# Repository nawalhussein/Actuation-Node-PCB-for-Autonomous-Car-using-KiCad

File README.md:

# STM32 Actuator Control Board PCB

This project contains the complete hardware design (schematics and PCB layout) and associated software for a custom-built STM32-based actuator control system to be put in the autonomous car.

### Brief Project Description

This PCB is designed as a centralized control hub for multiple DC motor actuators in an autonomous or complex electro-mechanical system (e.g., an agribot, mobile robot, or robotic manipulator).

At its core is an STM32 "BluePill" microcontroller. The board interfaces with various components to manage complex movement:

* **Microcontroller:** An STM32F103 (BluePill) provides the processing logic.
* **Actuator Drivers:** Integrated circuits (represented by connectors in the current schematic iteration) control multiple DC motors with direction (`DIR`) and pulse-width modulation (`PWM`) speed signals.
* **Control Input:** It receives motion and velocity commands via a high-level **CAN bus** or standard **UART** serial communication.
* **Feedback (ADC):** Analog inputs monitor potentiometer-based sensors (e.g., steering and brake feedback) for precise position sensing.
* **Interface (DAC):** A Digital-to-Analog converter provides fine-tuned analog voltage output.
* **Level Shifting:** Bidirectional level shifters ensure logic compatibility between 3.3V signals (like `STEP_EN`, `DIR_REAR_BRAKE`) and other standard 5V peripherals.
* **Safety:** A robust protection circuit with a reverse-voltage blocking diode and a fast-acting fuse ensures system reliability.
* **Expandability:** Multiple power sources and extra GPIO headers are included for external sensor integration and future features.

---

### Project Repository Contents

* `/hardware/`: Kicad design files (schematic and PCB)
* `/docs/`: PDF for the PCB and schematic

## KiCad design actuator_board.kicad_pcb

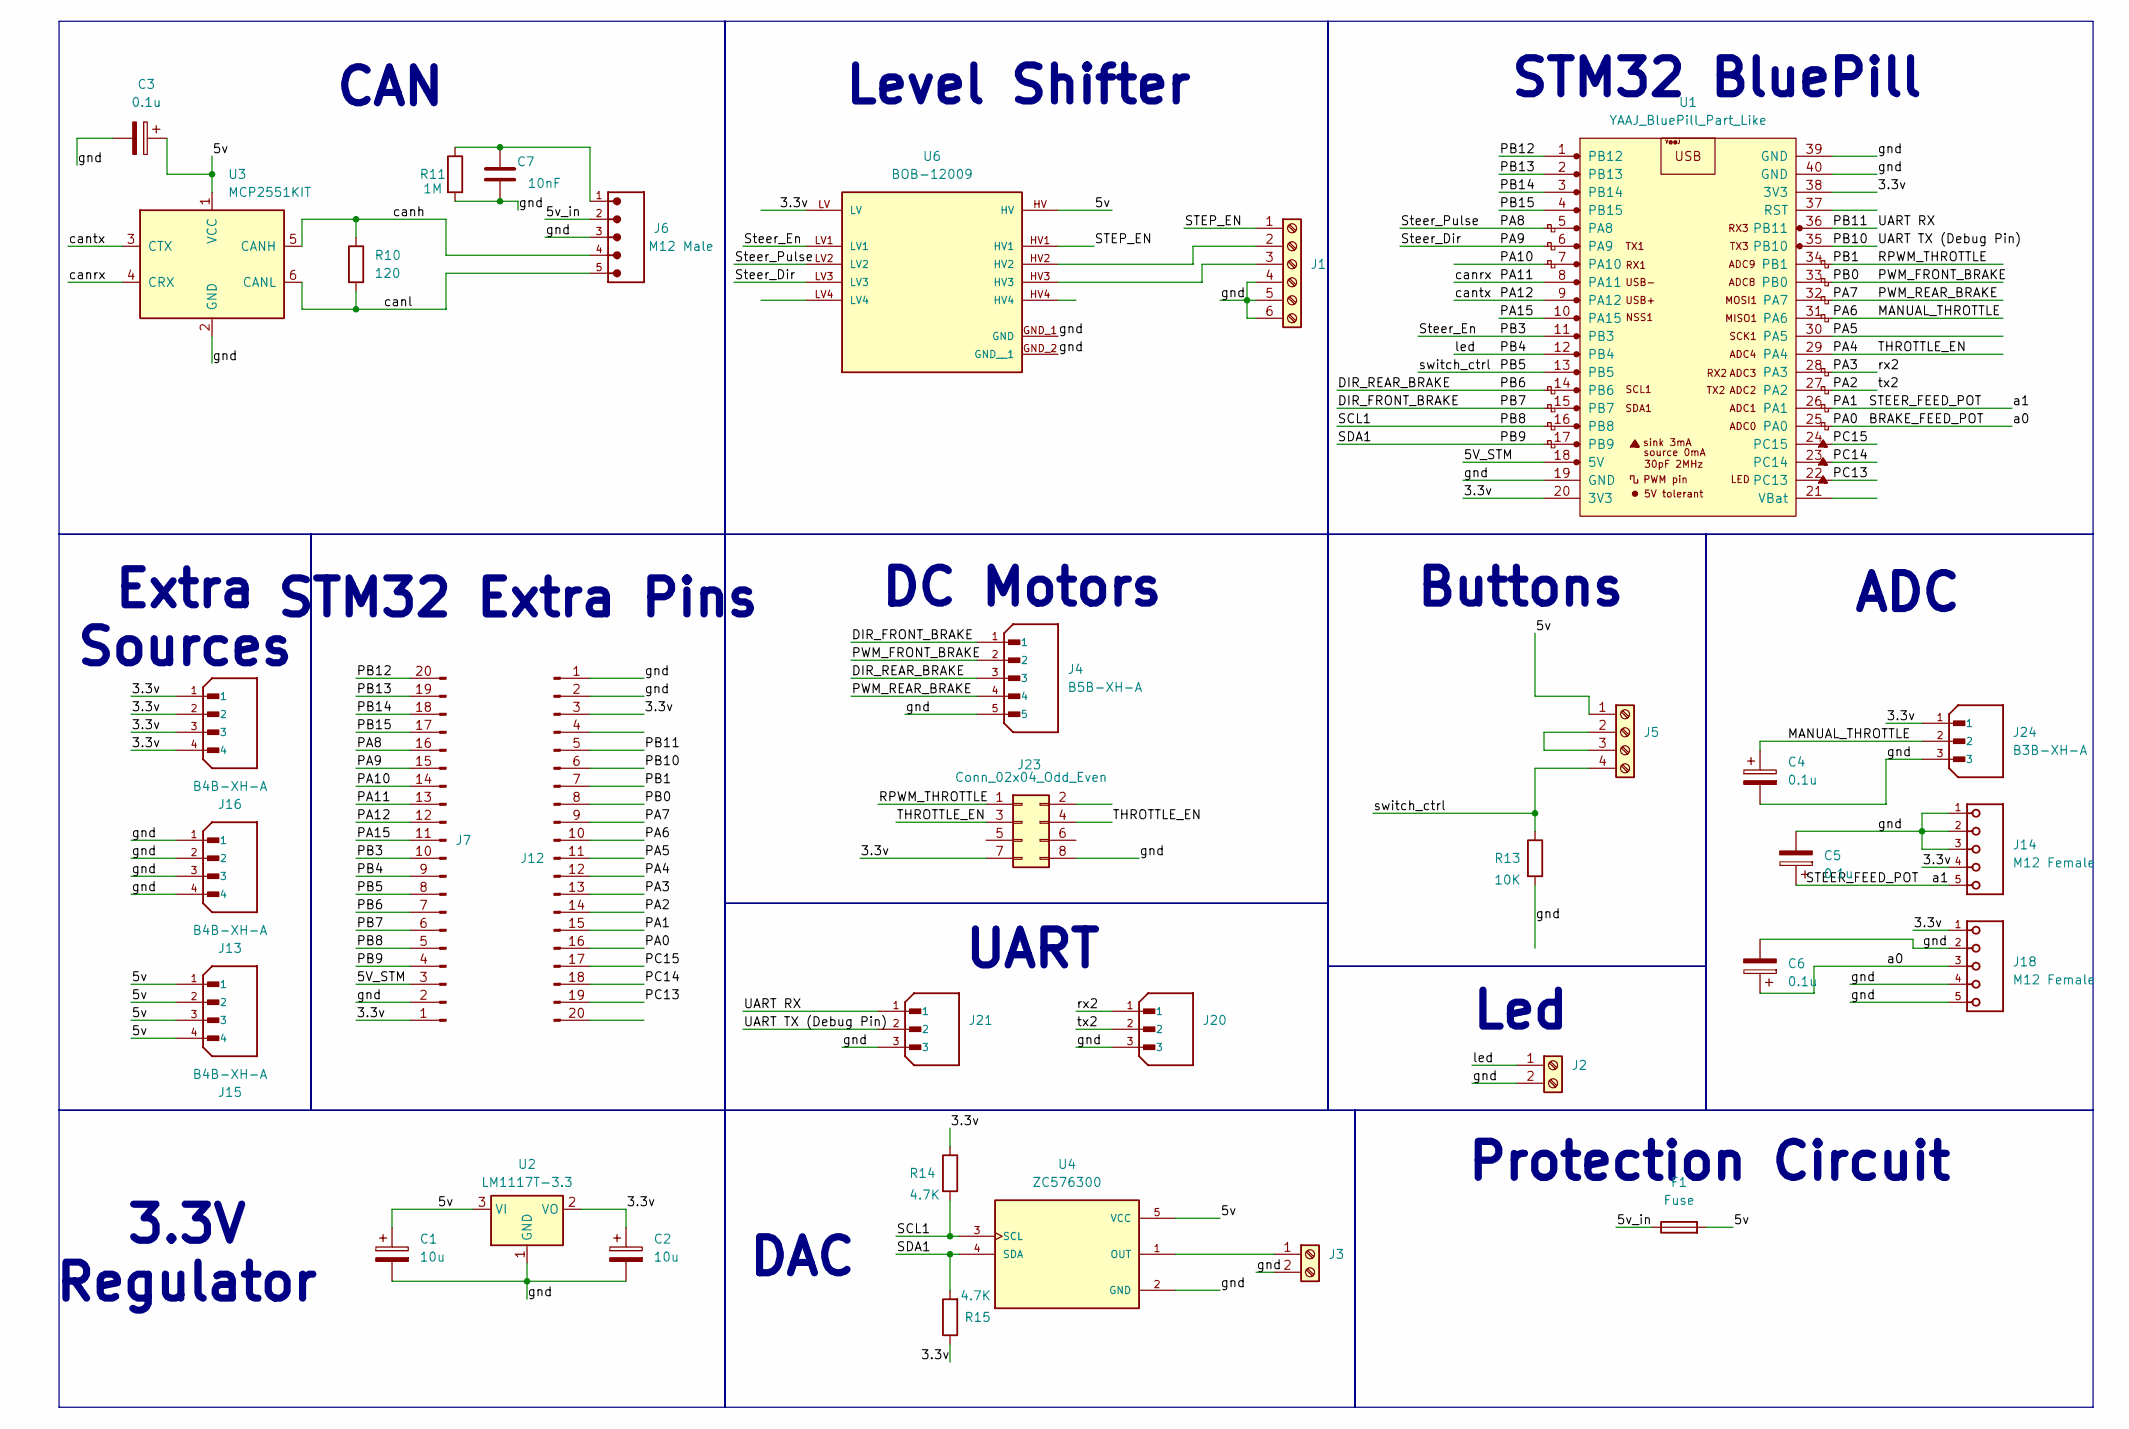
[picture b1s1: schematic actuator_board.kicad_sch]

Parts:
C1, C2: 10u; C_Disc_D6.0mm_W2.5mm_P5.00mm
C3, C4, C5, C6: 0.1u; C_Disc_D6.0mm_W2.5mm_P5.00mm
C7: 10nF; C_Disc_D6.0mm_W2.5mm_P5.00mm
F1: Fuse; Fuseholder_Cylinder-5x20mm_Schurter_0031_8201_Horizontal_Op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
J1: Screw_Terminal_01x06; TerminalBlock_Phoenix_MKDS-1,5-6-5.08_1x06_P5.08mm_Horizont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
J2, J3: Screw_Terminal_01x02; TE_282841-2
J4: B5B-XH-A; JST_B5B-XH-A; PARTREV 7/4/21
J5: Screw_Terminal_01x04; TE_282837-4
J6: M12 Male; 643270100305
J7, J12: Conn_01x20_Pin; PinSocket_1x20_P2.54mm_Vertical
J13, J15, J16: B4B-XH-A; JST_B4B-XH-A; PARTREV .
J14, J18: M12 Female; 643280100305
J20, J21, J24: B3B-XH-A; JST_B3B-XH-A; PARTREV .
J23: Conn_02x04_Odd_Even; IDC-Header_2x04_P2.54mm_Vertical
R10: 120; R_Axial_DIN0207_L6.3mm_D2.5mm_P10.16mm_Horizontal
R11: 1M; R_Axial_DIN0207_L6.3mm_D2.5mm_P10.16mm_Horizontal
R13: 10K; R_Axial_DIN0207_L6.3mm_D2.5mm_P10.16mm_Horizontal
R14, R15: 4.7K; R_Axial_DIN0207_L6.3mm_D2.5mm_P10.16mm_Horizontal
U1: YAAJ_BluePill_Part_Like; YAAJ_BluePill_1
U2: LM1117T-3.3; TO-220-3_Vertical
U3: MCP2551KIT; mcp2551kit
U4: ZC576300; MODULE_ZC576300; PARTREV v14
U6: BOB-12009; CONV_BOB-12009; PARTREV 01

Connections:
/3.3v: C2.1, J7.1, J12.3, J14.4, J16.1, J16.2, J16.3, J16.4, J18.1, J23.7, J24.1, R14.1, R15.1, U1.20 (3V3), U1.38 (3V3), U2.2 (VO), U6.LV
/5V_STM: J7.3, U1.18 (5V)
/5v: C1.1, C3.1, F1.2, J5.1, J15.1, J15.2, J15.3, J15.4, U2.3 (VI), U3.1 (VCC), U4.5 (VCC), U6.HV
/5v_in: F1.1, J6.2
/BRAKE_FEED_POT: C6.1, J12.16, J18.3, U1.25 (PA0)
/DIR_FRONT_BRAKE: J4.1, J7.6, U1.15 (PB7)
/DIR_REAR_BRAKE: J4.3, J7.7, U1.14 (PB6)
/MANUAL_THROTTLE: C4.1, J12.10, J24.2, U1.31 (PA6)
/PA1: C5.1, J12.15, J14.5, U1.26 (PA1)
/PA2: J12.14, J20.2, U1.27 (PA2)
/PA3: J12.13, J20.1, U1.28 (PA3)
/PA4: J12.12, J23.3, J23.4, U1.29 (PA4)
/PA5: J12.11, U1.30 (PA5)
/PA7: J4.4, J12.9, U1.32 (PA7)
/PA8: J7.16, U1.5 (PA8), U6.LV2
/PA9: J7.15, U1.6 (PA9), U6.LV3
/PA10: J7.14, U1.7 (PA10)
/PA11: J7.13, U1.8 (PA11), U3.4 (CRX)
/PA12: J7.12, U1.9 (PA12), U3.3 (CTX)
/PA15: J7.11, U1.10 (PA15)
/PB0: J4.2, J12.8, U1.33 (PB0)
/PB1: J12.7, J23.1, U1.34 (PB1)
/PB3: J7.10, U1.11 (PB3), U6.LV1
/PB4: J2.1, J7.9, U1.12 (PB4)
/PB5: J5.4, J7.8, R13.1, U1.13 (PB5)
/PB8: J7.5, R14.2, U1.16 (PB8), U4.3 (SCL)
/PB9: J7.4, R15.2, U1.17 (PB9), U4.4 (SDA)
/PB10: J12.6, J21.2, U1.35 (PB10)
/PB11: J12.5, J21.1, U1.36 (PB11)
/PB12: J7.20, U1.1 (PB12)
/PB13: J7.19, U1.2 (PB13)
/PB14: J7.18, U1.3 (PB14)
/PB15: J7.17, U1.4 (PB15)
/PC13: J12.19, U1.22 (PC13)
/PC14: J12.18, U1.23 (PC14)
/PC15: J12.17, U1.24 (PC15)
/STEP_EN: J1.1, U6.HV1
/canh: J6.4, R10.1, U3.5 (CANH)
/canl: J6.5, R10.2, U3.6 (CANL)
GND: C1.2, C2.2, C3.2, C4.2, C5.2, C6.2, C7.2, J1.4, J1.5, J1.6, J2.2, J3.2, J4.5, J6.3, J7.2, J12.1, J12.2, J13.1, J13.2, J13.3, J13.4, J14.1, J14.2, J14.3, J18.2, J18.4, J18.5, J20.3, J21.3, J23.8, J24.3, R11.2, R13.2, U1.19 (GND), U1.39 (GND), U1.40 (GND), U2.1 (GND), U3.2 (GND), U4.2 (GND), U4.6 (GND), U6.GND_1 (GND), U6.GND_2 (GND__1)
unnamed: C7.1, J6.1, R11.1
unnamed: J1.2, U6.HV2
unnamed: J1.3, U6.HV3
unnamed: J3.1, U4.1 (OUT)
unnamed: J5.2, J5.3

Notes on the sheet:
DC Motors
CAN
UART
STM32 Extra Pins
STM32 BluePill
ADC
Led
Level Shifter
Protection Circuit
DAC
Extra Sources
3.3V Regulator
Buttons

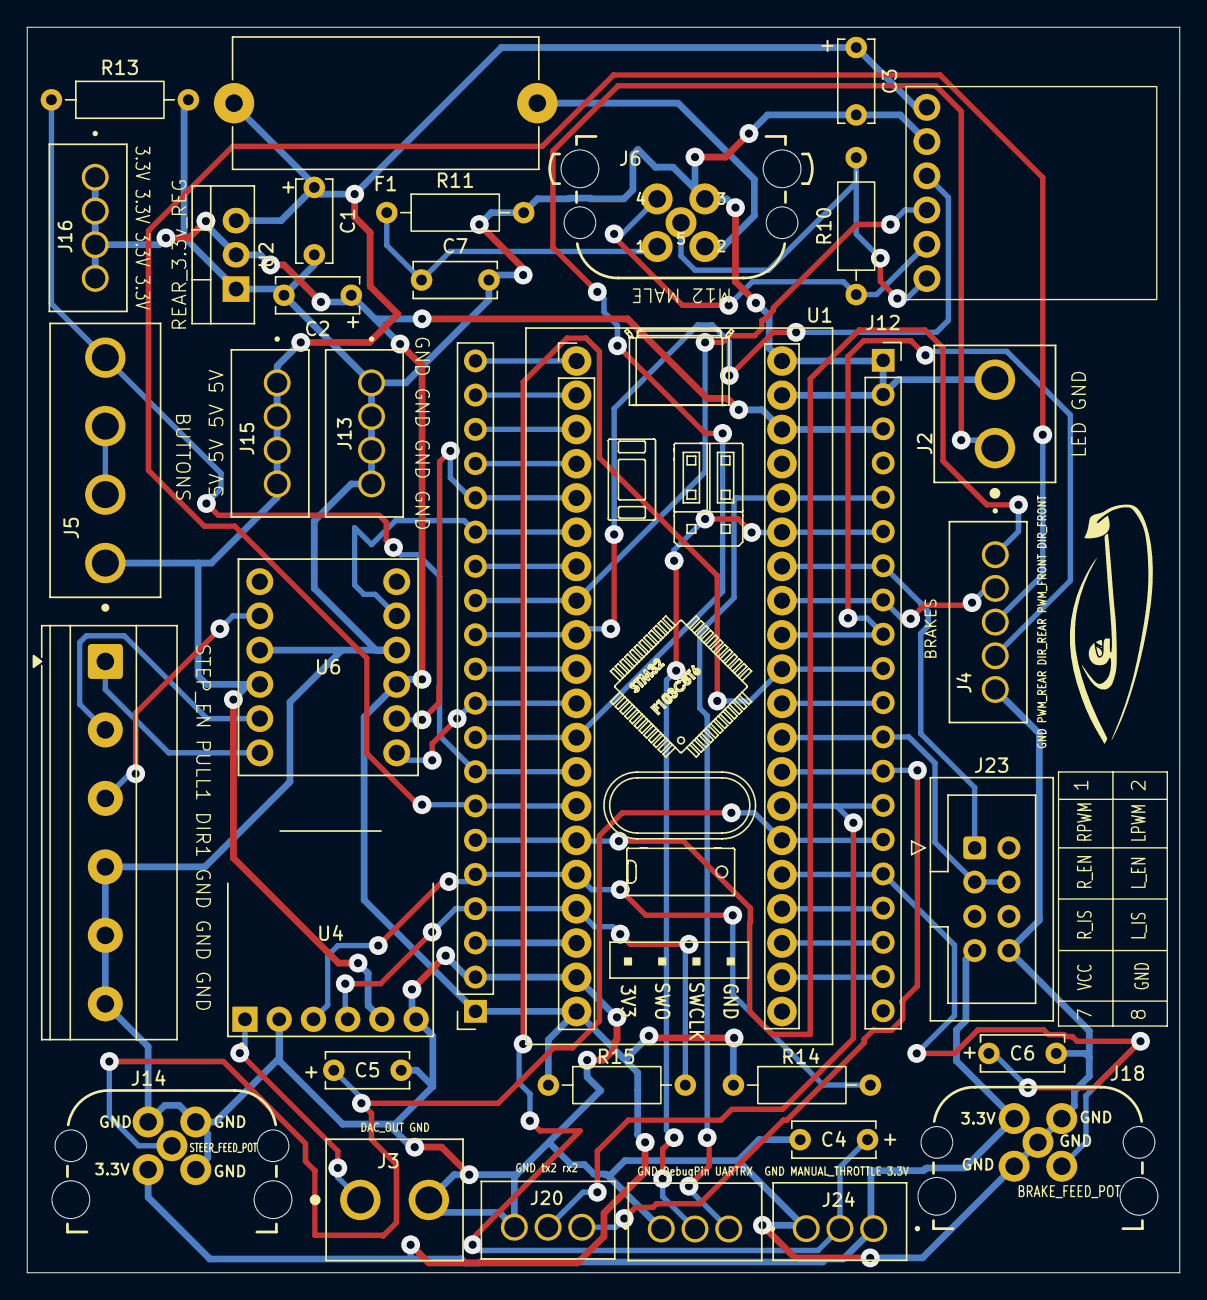
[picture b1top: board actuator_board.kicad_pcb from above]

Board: 2 copper layers, 85.5 x 92.4 mm, 35 parts (0 on the bottom side), 45 nets.

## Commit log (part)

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2026-06-22 Added KiCad Files
